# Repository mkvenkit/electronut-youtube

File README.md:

# electronut-youtube
Projects from the Electronut Labs Youtube Channel

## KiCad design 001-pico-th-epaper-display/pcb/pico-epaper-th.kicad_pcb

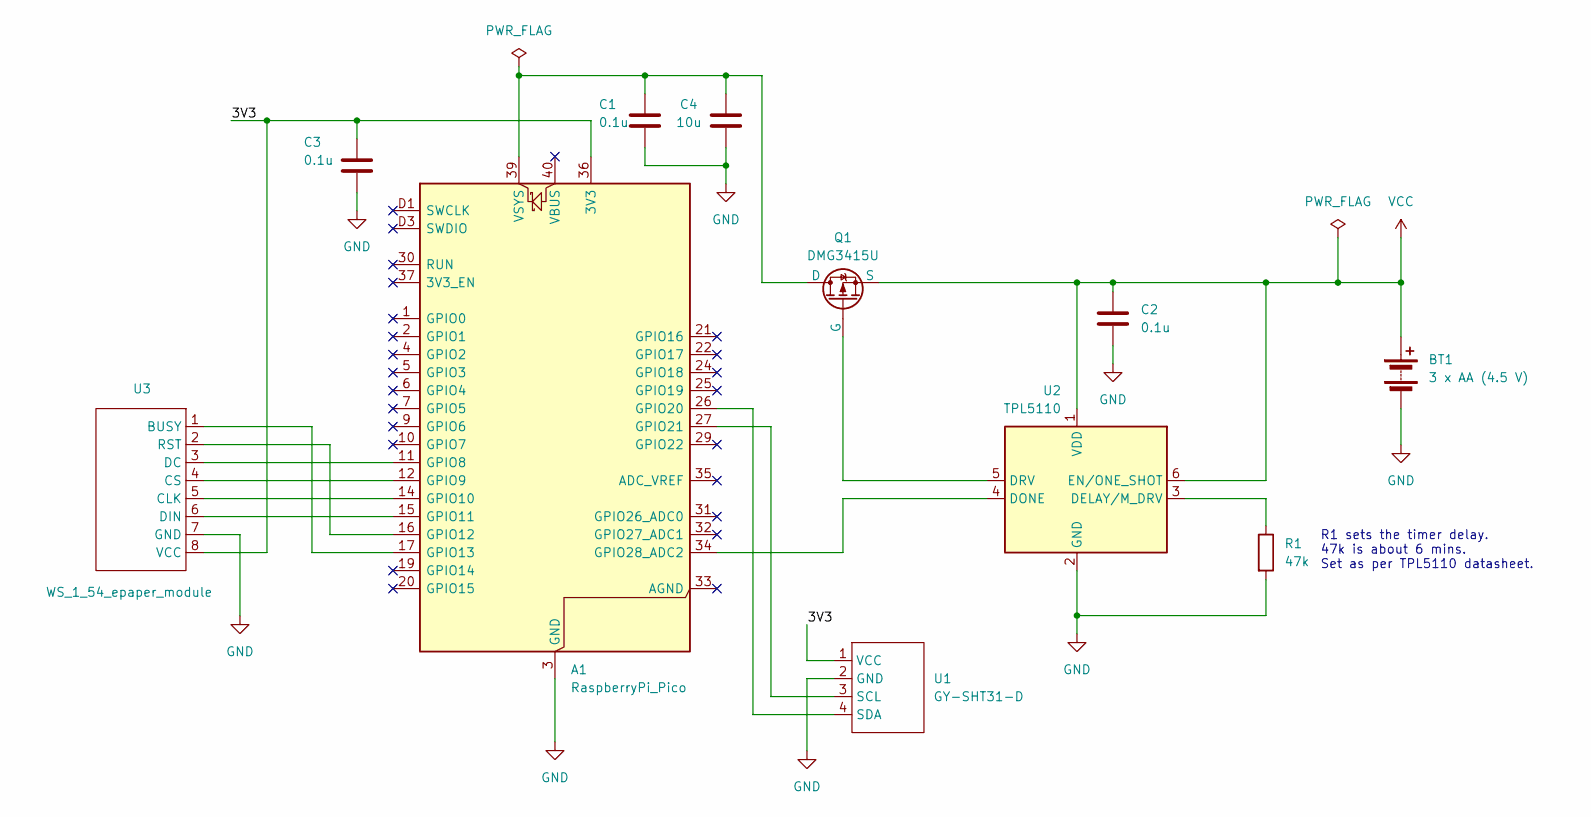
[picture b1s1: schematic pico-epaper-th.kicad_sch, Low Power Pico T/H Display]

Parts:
A1: RaspberryPi_Pico; RaspberryPi_Pico_SMD_HandSolder
BT1: 3 x AA (4.5 V); PinHeader_1x02_P2.54mm_Vertical
C1, C2, C3: 0.1u; C_0603_1608Metric_Pad1.08x0.95mm_HandSolder
C4: 10u; C_0603_1608Metric_Pad1.08x0.95mm_HandSolder
Q1: DMG3415U; SOT-23_Handsoldering
R1: 47k; R_0603_1608Metric_Pad0.98x0.95mm_HandSolder
U1: GY-SHT31-D; PinHeader_1x04_P2.54mm_Vertical
U2: TPL5110; SOT-23-6
U3: WS_1_54_epaper_module; PinHeader_1x08_P2.54mm_Vertical

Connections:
/3V3: A1.36 (3V3), C3.1, U1.1 (VCC), U3.8 (VCC)
GND: A1.3 (GND), A1.8 (GND), A1.13 (GND), A1.18 (GND), A1.23 (GND), A1.28 (GND), A1.38 (GND), A1.D2 (GND), BT1.2 (-), C1.2, C2.2, C3.2, C4.2, R1.2, U1.2 (GND), U2.2 (GND), U3.7 (GND)
unnamed: A1.11 (GPIO8), U3.3 (DC)
unnamed: A1.12 (GPIO9), U3.4 (CS)
unnamed: A1.14 (GPIO10), U3.5 (CLK)
unnamed: A1.15 (GPIO11), U3.6 (DIN)
unnamed: A1.16 (GPIO12), U3.2 (RST)
unnamed: A1.17 (GPIO13), U3.1 (BUSY)
unnamed: A1.26 (GPIO20), U1.4 (SDA)
unnamed: A1.27 (GPIO21), U1.3 (SCL)
unnamed: A1.34 (GPIO28_ADC2), U2.4 (DONE)
unnamed: A1.39 (VSYS), C1.1, C4.1, Q1.3 (D)
unnamed: Q1.1 (G), U2.5 (DRV)
unnamed: R1.1, U2.3 (DELAY/M_DRV)
VCC: BT1.1 (+), C2.1, Q1.2 (S), U2.1 (VDD), U2.6 (EN/ONE_SHOT)

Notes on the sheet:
R1 sets the timer delay. 47k is about 6 mins. Set as per TPL5110 datasheet.

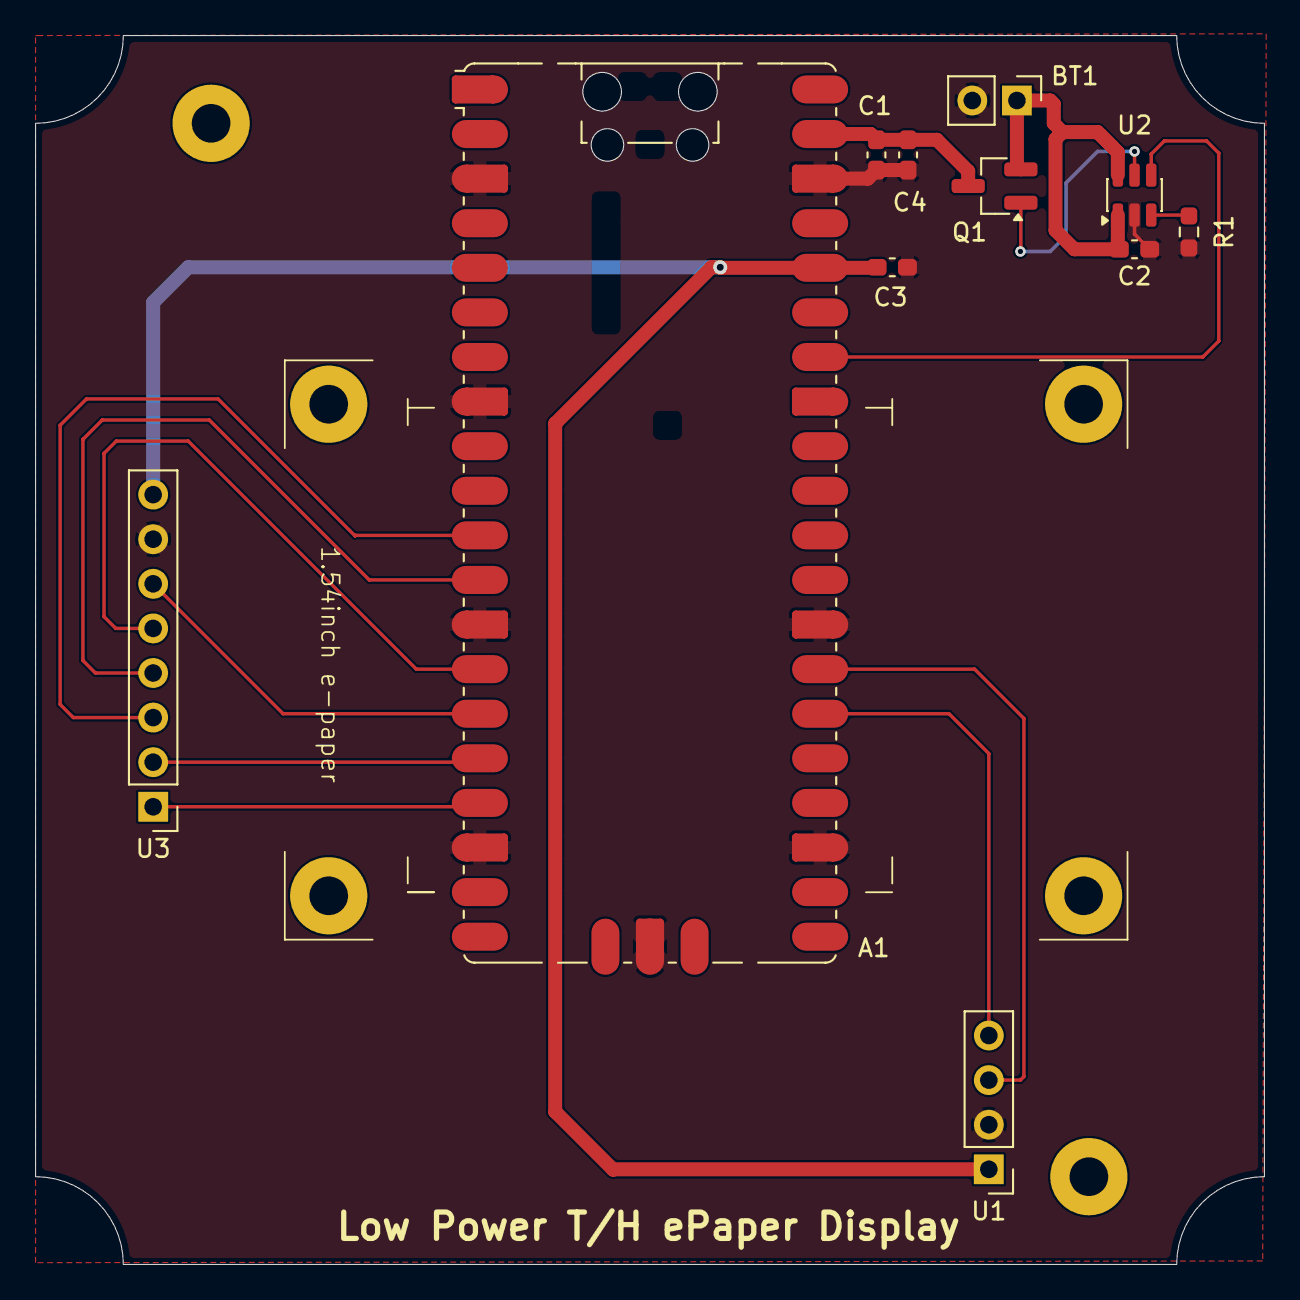
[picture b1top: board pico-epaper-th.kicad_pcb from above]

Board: 2 copper layers, 70.0 x 70.0 mm, 11 parts (0 on the bottom side), 15 nets.

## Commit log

2026-04-10 ignore
2026-04-10 added firmware
2026-04-11 fw updated
2026-04-11 added docs
2026-04-11 fw updated
    1. done signal
    2. start up issues
2026-04-12 updated pcb design
2026-04-12 switched DONE to GP28 for ease of routing
2026-04-12 updated pcb
2026-04-19 pcb updated
2026-04-19 added curved corners
2026-04-19 added epaper 3d
2026-04-19 added battery
2026-04-20 name change
2026-04-20 pin changed for sht31
2026-04-21 updated docs
2026-04-21 turn of led
2026-04-21 update docs
2026-04-21 schematic updated
2026-04-22 pcb routing
2026-04-22 pcb rounting
2026-04-25 updated trace
2026-04-25 fixed drc errors on pcb
2026-04-27 removed locked silk
2026-04-27 added yt url
2026-04-28 added ver
2026-04-28 gerbers
2026-04-30 4 q display
2026-04-30 rotated display by 90 deg cw
2026-05-03 clean up
2026-05-07 turn leds off
